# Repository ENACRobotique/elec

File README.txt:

Repository for electronic circuits design

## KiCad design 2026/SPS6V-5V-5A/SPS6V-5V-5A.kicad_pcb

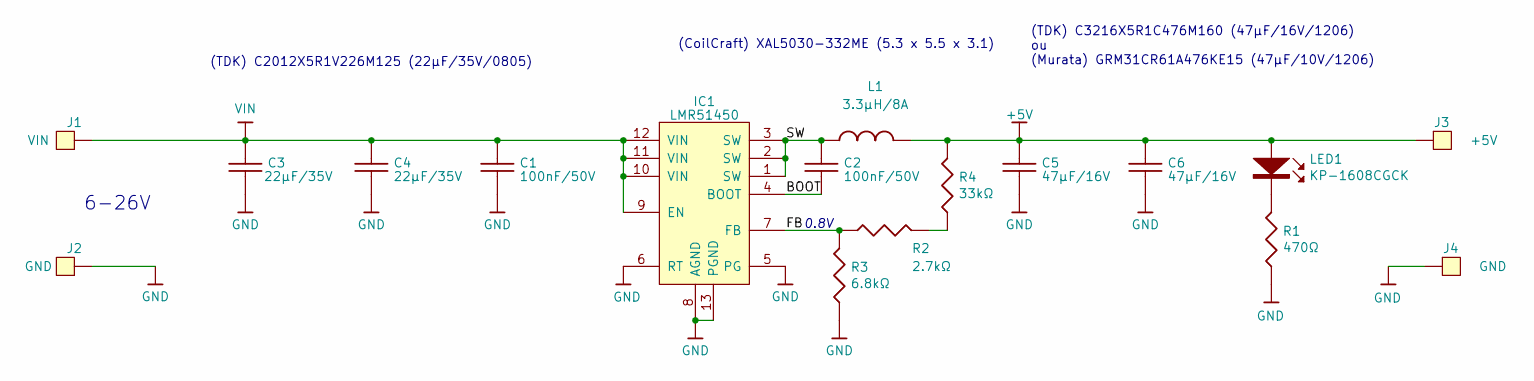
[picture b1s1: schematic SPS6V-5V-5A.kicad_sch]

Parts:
C1, C2: 100nF/50V; C_0603
C3, C4: 22µF/35V; C_0805
C5, C6: 47µF/16V; C_1206
IC1: LMR51450
J1: VIN; power_PAD_THT
J2, J4: GND; power_PAD_THT
J3: +5V; power_PAD_THT
L1: 3.3µH/8A; XAL5030
LED1: KP-1608CGCK
R1: 470Ω; R_0603
R2: 2.7kΩ; R_0603
R3: 6.8kΩ; R_0603
R4: 33kΩ; R_0603

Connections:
+5V: C5.1, C6.1, J3.1, L1.2, LED1.2 (A), R4.1
/BOOT: C2.2, IC1.4 (BOOT)
/FB: IC1.7 (FB), R2.2, R3.1
/SW: C2.1, IC1.1 (SW), IC1.2 (SW), IC1.3 (SW), L1.1
GND: C1.2, C3.2, C4.2, C5.2, C6.2, IC1.5 (PG), IC1.6 (RT), IC1.8 (AGND), IC1.13 (PGND), J2.1, J4.1, R1.2, R3.2
unnamed: LED1.1 (K), R1.1
unnamed: R2.1, R4.2
VIN: C1.1, C3.1, C4.1, IC1.9 (EN), IC1.10 (VIN), IC1.11 (VIN), IC1.12 (VIN), J1.1

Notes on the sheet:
(TDK) C2012X5R1V226M125 (22µF/35V/0805)
(TDK) C3216X5R1C476M160 (47µF/16V/1206) ou (Murata) GRM31CR61A476KE15 (47µF/10V/1206)
(CoilCraft) XAL5030-332ME (5.3 x 5.5 x 3.1)
6-26V
0.8V

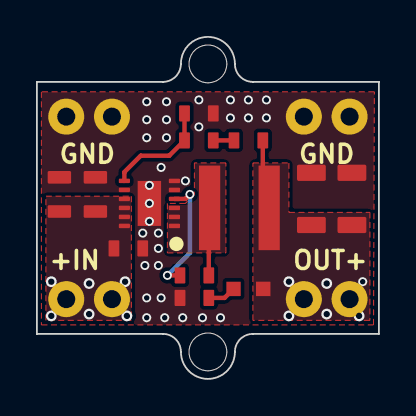
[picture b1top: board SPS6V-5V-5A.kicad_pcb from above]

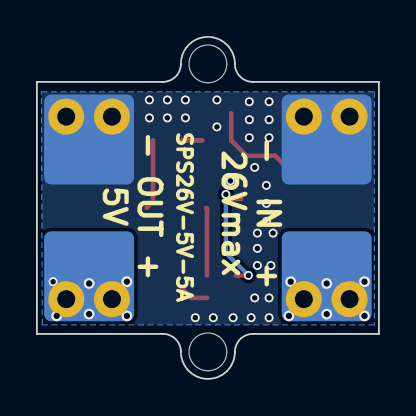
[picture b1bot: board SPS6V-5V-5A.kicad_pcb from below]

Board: 2 copper layers, 19.0 x 19.0 mm, 17 parts (4 on the bottom side), 8 nets.

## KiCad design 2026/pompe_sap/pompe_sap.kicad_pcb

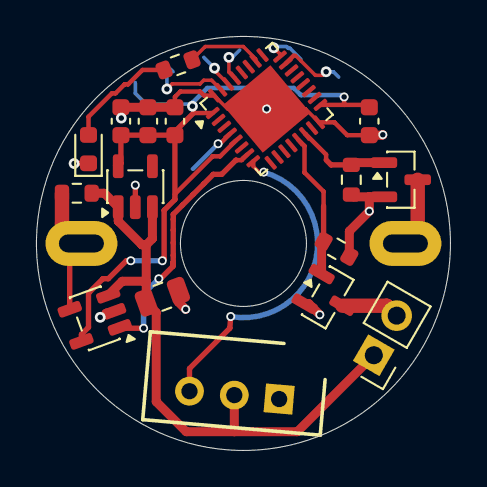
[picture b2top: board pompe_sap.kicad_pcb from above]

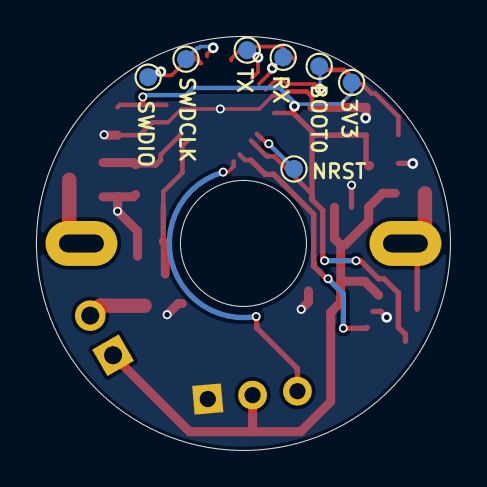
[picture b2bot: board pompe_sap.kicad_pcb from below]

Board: 2 copper layers, 23.0 x 23.0 mm, 25 parts (7 on the bottom side), 18 nets.

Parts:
C1: C 1uf; C_0805_2012Metric
C2: C 1uf; C_0603_1608Metric
C3: 4U7; C_0603_1608Metric
C4, C5: 100n; C_0603_1608Metric
D1: LED; LED_0603_1608Metric
J1: Conn_01x02_Pin; PinHeader_1x02_P2.54mm_Vertical
J2: 22-03-5035; SHDR3W70P0X250_1X3_990X490X590P
Q1, Q2: IRLML6344 (modèle du 6244); SOT-23
R1: Rsens; R_0603_1608Metric
R2: 390; R_0603_1608Metric
R4, R5: 100K; R_0603_1608Metric
TP1: SWDIO_TP; TestPoint_Pad_D1.0mm
TP2: SWDCLK_TP; TestPoint_Pad_D1.0mm
TP3: NRST_TP; TestPoint_Pad_D1.0mm
TP4: 3V3_TP; TestPoint_Pad_D1.0mm
TP5: BOOT0_TP; TestPoint_Pad_D1.0mm
TP6: U1_TX; TestPoint_Pad_D1.0mm
TP7: U1_RX; TestPoint_Pad_D1.0mm
U1: pompe
U2: NCP718xSN120; SOT-23-5
U3: INA180A1; SOT-23-5
U4: STM32L432KCUx; QFN-32-1EP_5x5mm_P0.5mm_EP3.45x3.45mm

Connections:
+3V3: C2.1, C3.1, C4.1, C5.1, TP4.1, U2.5 (OUT), U3.5 (V+), U4.1 (VDD), U4.5 (VDDA), U4.17 (VDD)
+12V: C1.1, J1.1, J2.2, R1.1, U2.1 (IN), U2.3 (EN), U3.3 (+)
/BOOT0: TP5.1, U4.31 (PH3)
/NRST: TP3.1, U4.4 (NRST)
/SWDCLK: TP2.1, U4.24 (PA14)
/SWDIO: TP1.1, U4.23 (PA13)
GND: C1.2, C2.2, C3.2, C4.2, C5.2, D1.1 (K), J2.1, Q1.2 (S), Q2.2 (S), R4.2, R5.2, U2.2 (GND), U3.2 (GND), U4.16 (VSS), U4.32 (VSS), U4.33 (VSS)
unnamed: D1.2 (A), R2.1
unnamed: J1.2, Q2.3 (D)
unnamed: Q1.3 (D), U1.2
unnamed: R1.2, U1.1, U3.4 (-)
unnamed: R2.2, U4.26 (PB3)
unnamed: TP6.1, U4.29 (PB6)
unnamed: TP7.1, U4.30 (PB7)
PUMP: Q1.1 (G), R4.1, U4.14 (PB0)
UART_TX: J2.3, U4.8 (PA2)
VALVE: Q2.1 (G), R5.1, U4.13 (PA7)
Vout: U3.1, U4.7 (PA1)

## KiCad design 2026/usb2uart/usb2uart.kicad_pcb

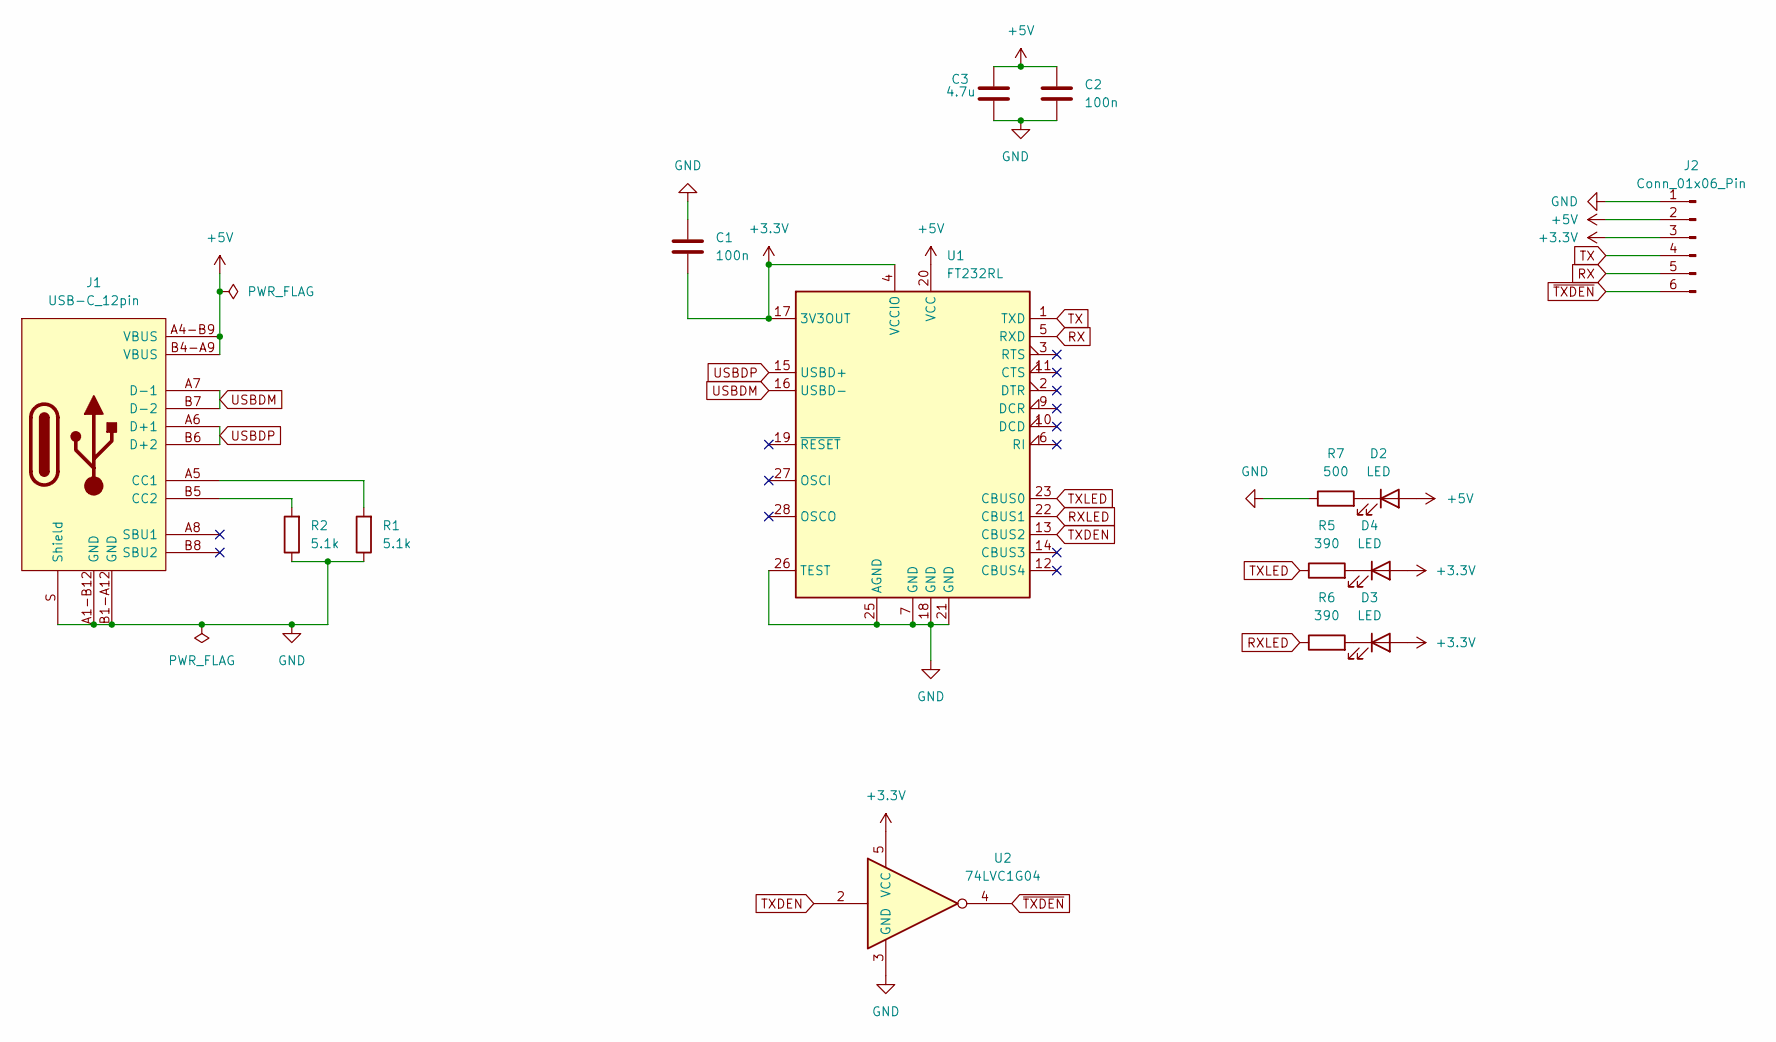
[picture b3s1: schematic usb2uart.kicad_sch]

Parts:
C1, C2: 100n; C_0603_1608Metric
C3: 4.7u; CP_EIA-3216-18_Kemet-A
D2, D3, D4: LED; LED_0603_1608Metric
J1: USB-C_12pin; USB-C_HRO_C-31-M-12
J2: Conn_01x06_Pin; Molex_PicoBlade_53047-0610_1x06_P1.25mm_Vertical
R1, R2: 5.1k; R_0603_1608Metric
R5, R6: 390; R_0603_1608Metric
R7: 500; R_0603_1608Metric
U1: FT232RL; SSOP-28_5.3x10.2mm_P0.65mm
U2: 74LVC1G04; SOT-23-5

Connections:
+3.3V: C1.2, D3.2 (A), D4.2 (A), J2.3, U1.4 (VCCIO), U1.17 (3V3OUT), U2.5 (VCC)
+5V: C2.1, C3.2, D2.2 (A), J1.A4-B9 (VBUS), J1.B4-A9 (VBUS), J2.2, U1.20 (VCC)
GND: C1.1, C2.2, C3.1, J1.A1-B12 (GND), J1.B1-A12 (GND), J1.S (Shield), J2.1, R1.1, R2.1, R7.1, U1.7 (GND), U1.18 (GND), U1.21 (GND), U1.25 (AGND), U1.26 (TEST), U2.3 (GND)
unnamed: D2.1 (K), R7.2
unnamed: D3.1 (K), R6.2
unnamed: D4.1 (K), R5.2
unnamed: J1.A5 (CC1), R1.2
unnamed: J1.B5 (CC2), R2.2
RX: J2.5, U1.5 (RXD)
RXLED: R6.1, U1.22 (CBUS1)
TX: J2.4, U1.1 (TXD)
TXDEN: U1.13 (CBUS2), U2.2
TXLED: R5.1, U1.23 (CBUS0)
USBDM: J1.A7 (D-1), J1.B7 (D-2), U1.16 (USBD-)
USBDP: J1.A6 (D+1), J1.B6 (D+2), U1.15 (USBD+)
~TXDEN: J2.6, U2.4

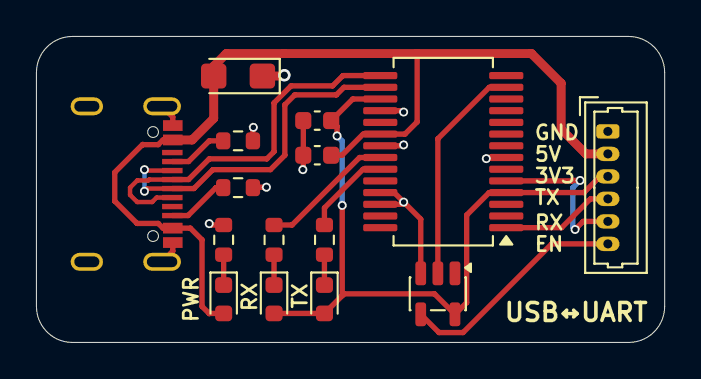
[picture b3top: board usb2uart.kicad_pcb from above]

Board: 2 copper layers, 34.9 x 17.0 mm, 15 parts (0 on the bottom side), 16 nets.

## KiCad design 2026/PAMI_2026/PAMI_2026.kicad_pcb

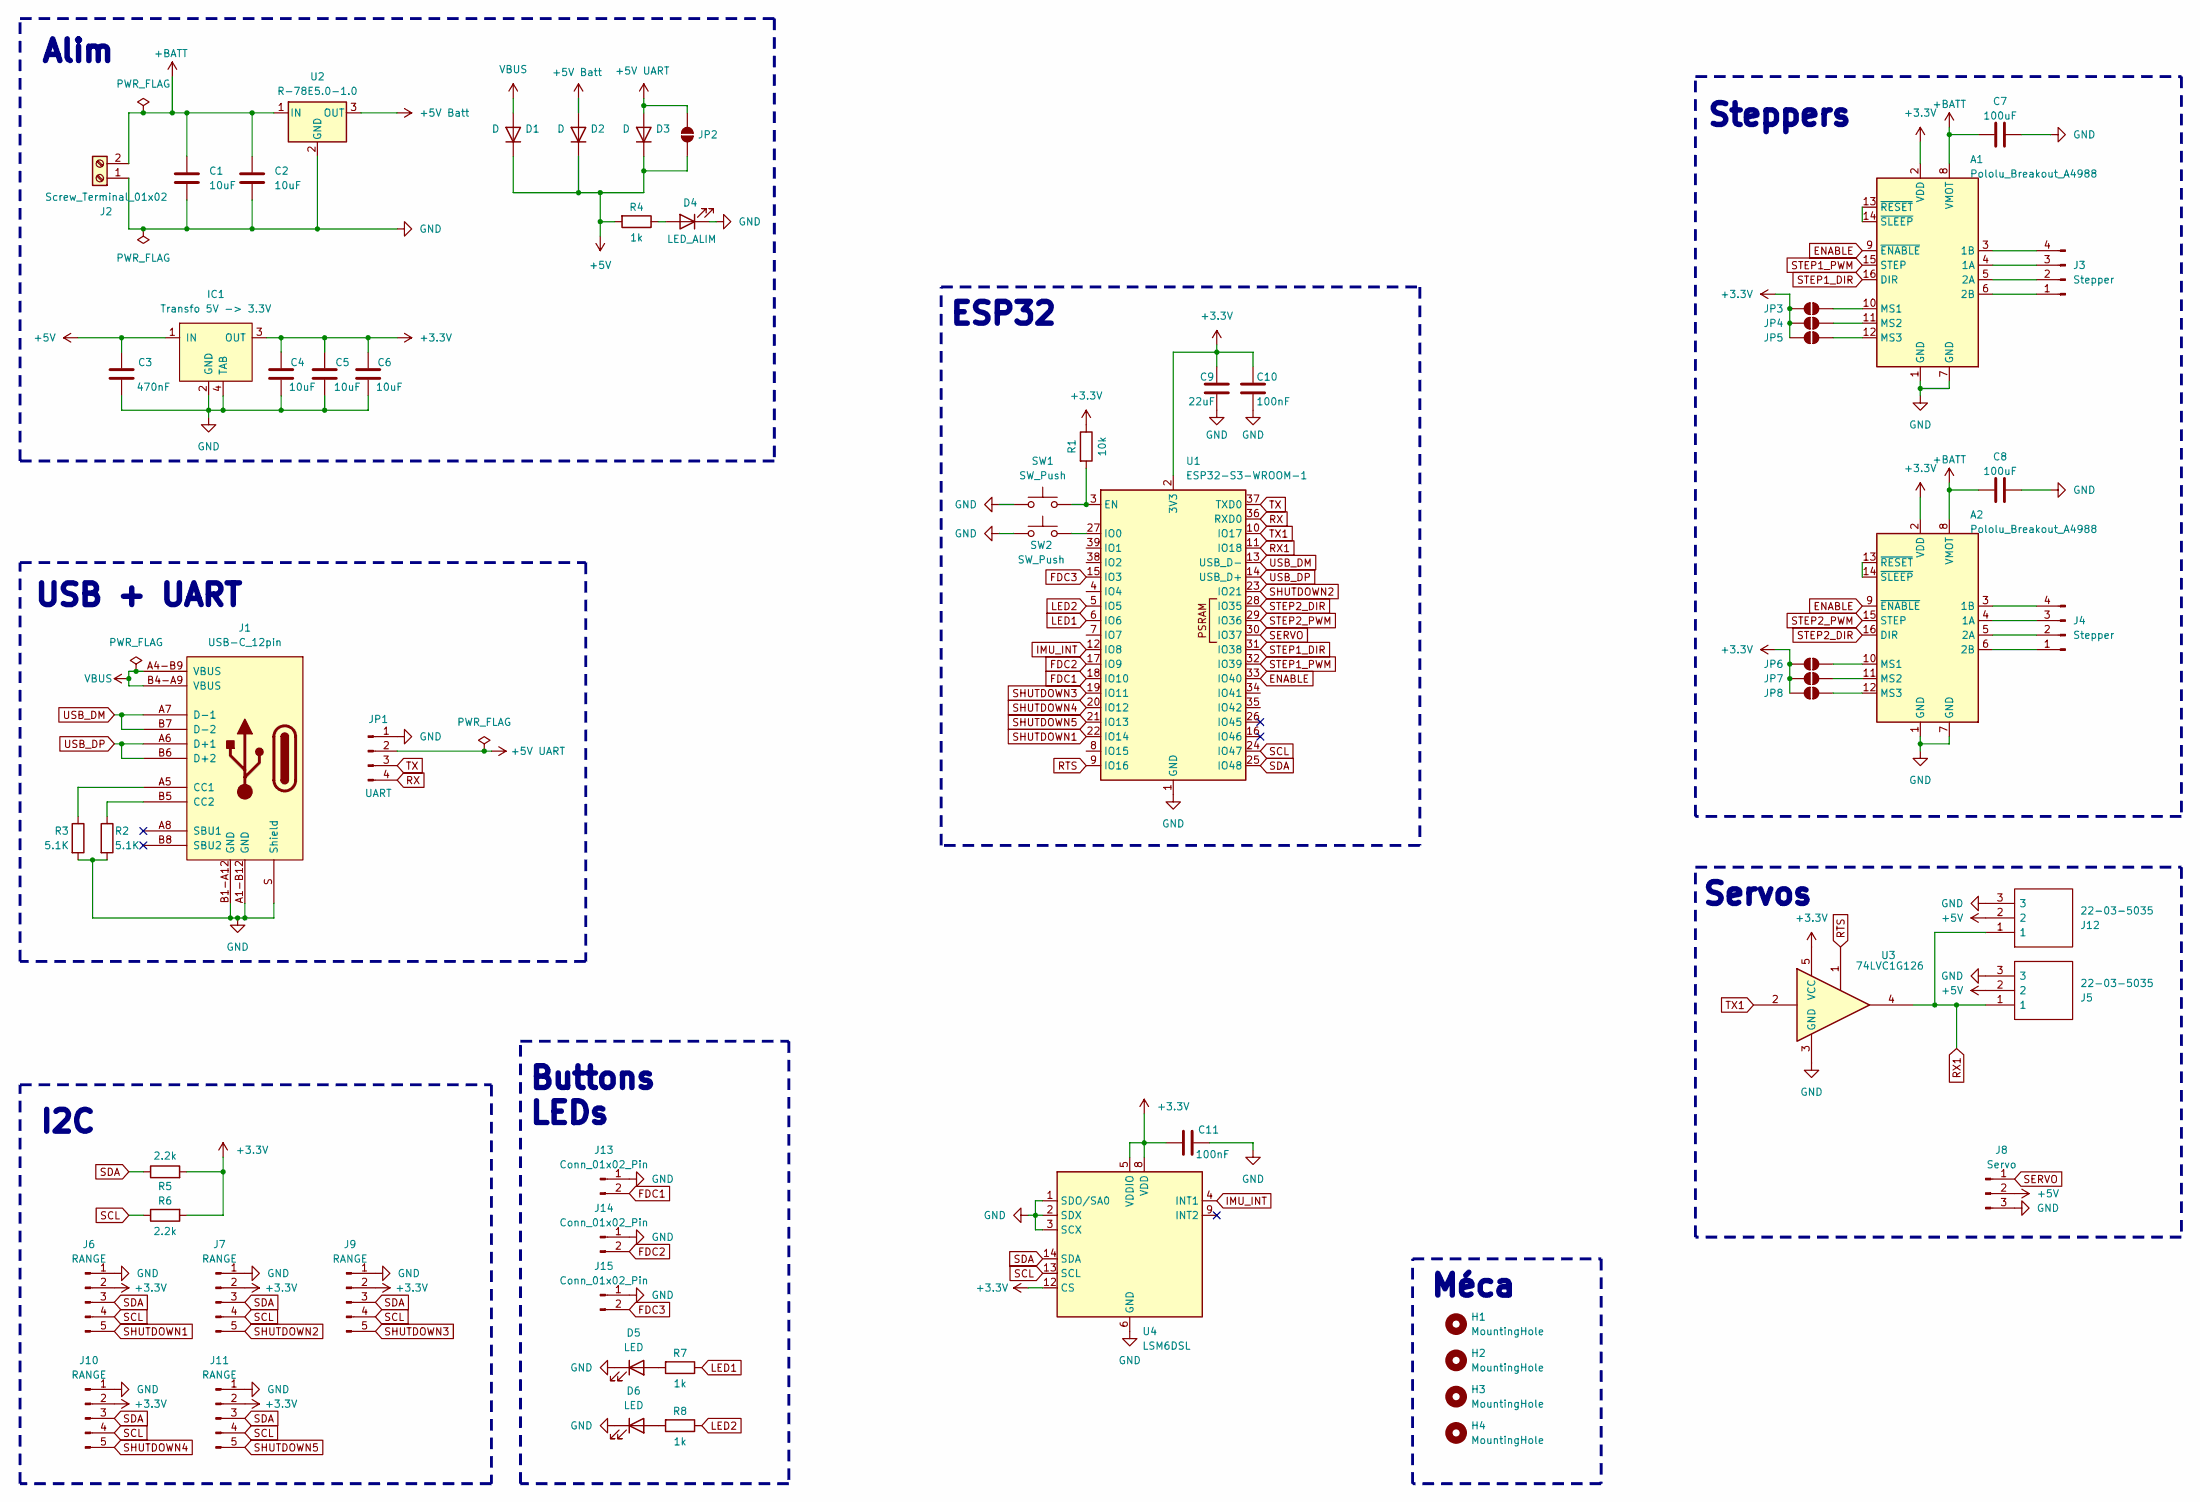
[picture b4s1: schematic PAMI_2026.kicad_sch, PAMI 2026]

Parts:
A1, A2: Pololu_Breakout_A4988; Pololu_Breakout-16_15.2x20.3mm
C1, C2: 10uF; C_0805_2012Metric
C3: 470nF; C_0603_1608Metric
C4, C5, C6: 10uF; C_0603_1608Metric
C7, C8: 100uF; CP_Elec_10x12.5
C9: 22uF; C_0805_2012Metric
C10, C11: 100nF; C_0603_1608Metric
D1, D2, D3: D; Nexperia_CFP3_SOD-123W
D4: LED_ALIM; LED_0603_1608Metric
D5, D6: LED; LED_0603_1608Metric
H1, H2, H3, H4: MountingHole; MountingHole_3.2mm_M3
IC1: Transfo 5V -> 3.3V; LM3940IMP
J1: USB-C_12pin; USB-C_HRO_C-31-M-12
J2: Screw_Terminal_01x02; TerminalBlock_MetzConnect_Type055_RT01502HDWU_1x02_P5.00mm_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
J3, J4: Stepper; PinHeader_1x04_P2.54mm_Vertical
J5, J12: 22-03-5035; SHDR3W70P0X250_1X3_990X490X590P; Manufacturer_Part_Number 22-03-5035; Mouser Part Number 538-22-03-5035
J6, J7, J9, J10, J11: RANGE; Molex_PicoBlade_53398-0571_1x05-1MP_P1.25mm_Vertical
J8: Servo; PinHeader_1x03_P2.54mm_Vertical
J13, J14, J15: Conn_01x02_Pin; PinHeader_1x02_P2.54mm_Vertical
JP1: UART; PinHeader_1x04_P2.54mm_Vertical
JP2: SolderJumper_2_Open; PinHeader_1x02_P2.54mm_Vertical
JP3, JP4, JP5, JP6, JP7, JP8: SolderJumper_2_Open; SolderJumper-2_P1.3mm_Open_TrianglePad1.0x1.5mm
R1: 10k; R_0603_1608Metric
R2, R3: 5.1K; R_0603_1608Metric
R4, R7, R8: 1k; R_0603_1608Metric
R5, R6: 2.2k; R_0603_1608Metric
SW1, SW2: SW_Push; SWITCH_DTSM31NV
U1: ESP32-S3-WROOM-1
U2: R-78E5.0-1.0; Converter_DCDC_RECOM_R-78E-0.5_THT
U3: 74LVC1G126; SOT-23-5
U4: LSM6DSL; LGA-14_3x2.5mm_P0.5mm_LayoutBorder3x4y

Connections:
+3.3V: A1.2 (VDD), A2.2 (VDD), C4.1, C5.1, C6.1, C9.1, C10.1, C11.1, IC1.3 (OUT), J6.2, J7.2, J9.2, J10.2, J11.2, JP3.1 (A), JP4.1 (A), JP5.1 (A), JP6.1 (A), JP7.1 (A), JP8.1 (A), R1.1, R5.2, R6.2, U1.2 (3V3), U3.5 (VCC), U4.5 (VDDIO), U4.8 (VDD), U4.12 (CS)
+5V: C3.1, D1.1 (K), D2.1 (K), D3.1 (K), IC1.1 (IN), J5.2, J8.2, J12.2, JP2.1 (A), R4.2
+5V Batt: D2.2 (A), U2.3 (OUT)
+5V UART: D3.2 (A), JP1.2, JP2.2 (B)
+BATT: A1.8 (VMOT), A2.8 (VMOT), C1.1, C2.1, C7.1, C8.1, J2.2, U2.1 (IN)
ENABLE: A1.9 (~ENABLE), A2.9 (~ENABLE), U1.33 (IO40)
FDC1: J13.2, U1.18 (IO10)
FDC2: J14.2, U1.17 (IO9)
FDC3: J15.2, U1.15 (IO3)
GND: A1.1 (GND), A1.7 (GND), A2.1 (GND), A2.7 (GND), C1.2, C2.2, C3.2, C4.2, C5.2, C6.2, C7.2, C8.2, C9.2, C10.2, C11.2, D4.1 (K), D5.1 (K), D6.1 (K), IC1.2 (GND), IC1.4 (TAB), J1.A1-B12 (GND), J1.B1-A12 (GND), J1.S (Shield), J2.1, J5.3, J6.1, J7.1, J8.3, J9.1, J10.1, J11.1, J12.3, J13.1, J14.1, J15.1, JP1.1, R2.2, R3.2, SW1.1, SW2.1, U1.1 (GND), U1.40 (GND), U1.41 (GND), U2.2 (GND), U3.3 (GND), U4.1 (SDO/SA0), U4.2 (SDX), U4.3 (SCX), U4.6 (GND), U4.7 (GND)
IMU_INT: U1.12 (IO8), U4.4 (INT1)
LED1: R7.1, U1.6 (IO6)
LED2: R8.1, U1.5 (IO5)
unnamed: A1.4 (1A), J3.3
unnamed: A1.3 (1B), J3.4
unnamed: A1.5 (2A), J3.2
unnamed: A1.6 (2B), J3.1
unnamed: A1.10 (MS1), JP3.2 (B)
unnamed: A1.11 (MS2), JP4.2 (B)
unnamed: A1.12 (MS3), JP5.2 (B)
unnamed: A1.13 (~RESET), A1.14 (~SLEEP)
unnamed: A2.4 (1A), J4.3
unnamed: A2.3 (1B), J4.4
unnamed: A2.5 (2A), J4.2
unnamed: A2.6 (2B), J4.1
unnamed: A2.10 (MS1), JP6.2 (B)
unnamed: A2.11 (MS2), JP7.2 (B)
unnamed: A2.12 (MS3), JP8.2 (B)
unnamed: A2.13 (~RESET), A2.14 (~SLEEP)
unnamed: D4.2 (A), R4.1
unnamed: D5.2 (A), R7.2
unnamed: D6.2 (A), R8.2
unnamed: J1.A5 (CC1), R3.1
unnamed: J1.B5 (CC2), R2.1
unnamed: R1.2, SW1.2, U1.3 (EN)
unnamed: SW2.2, U1.27 (IO0)
RTS: U1.9 (IO16), U3.1
RX: JP1.4, U1.36 (RXD0)
RX1: J5.1, J12.1, U1.11 (IO18), U3.4
SCL: J6.4, J7.4, J9.4, J10.4, J11.4, R6.1, U1.24 (IO47), U4.13 (SCL)
SDA: J6.3, J7.3, J9.3, J10.3, J11.3, R5.1, U1.25 (IO48), U4.14 (SDA)
SERVO: J8.1, U1.30 (IO37)
SHUTDOWN1: J6.5, U1.22 (IO14)
SHUTDOWN2: J7.5, U1.23 (IO21)
SHUTDOWN3: J9.5, U1.19 (IO11)
SHUTDOWN4: J10.5, U1.20 (IO12)
SHUTDOWN5: J11.5, U1.21 (IO13)
STEP1_DIR: A1.16 (DIR), U1.31 (IO38)
STEP1_PWM: A1.15 (STEP), U1.32 (IO39)
STEP2_DIR: A2.16 (DIR), U1.28 (IO35)
STEP2_PWM: A2.15 (STEP), U1.29 (IO36)
TX: JP1.3, U1.37 (TXD0)
TX1: U1.10 (IO17), U3.2
USB_DM: J1.A7 (D-1), J1.B7 (D-2), U1.13 (USB_D-)
USB_DP: J1.A6 (D+1), J1.B6 (D+2), U1.14 (USB_D+)
VBUS: D1.2 (A), J1.A4-B9 (VBUS), J1.B4-A9 (VBUS)

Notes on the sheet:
USB + UART
I2C
Buttons LEDs
Steppers
ESP32
Méca
Alim
Servos

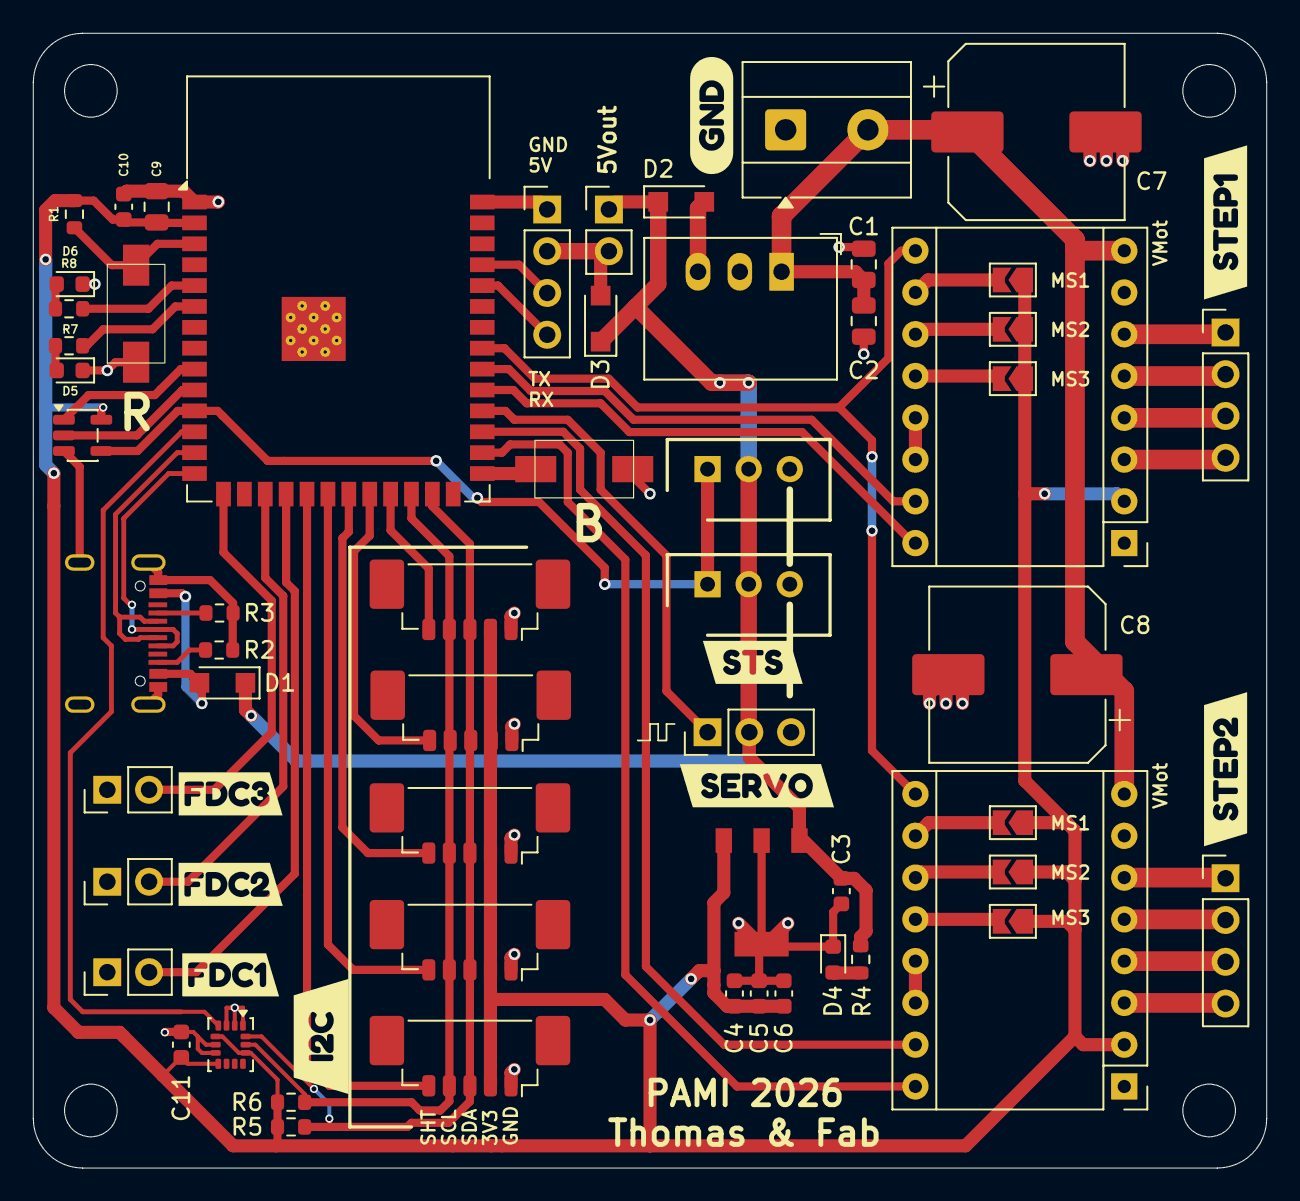
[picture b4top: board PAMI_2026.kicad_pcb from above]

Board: 2 copper layers, 75.0 x 69.0 mm, 70 parts (0 on the bottom side), 56 nets.

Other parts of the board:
kibuzzard-693B43A5: G***; kibuzzard-693B43A5
kibuzzard-693B44DB: G***; kibuzzard-693B44DB
kibuzzard-693B44EC: G***; kibuzzard-693B44EC
kibuzzard-693B45E1: G***; kibuzzard-693B45E1
kibuzzard-693B45FB: G***; kibuzzard-693B45FB
kibuzzard-693B4393: G***; kibuzzard-693B4393
kibuzzard-693B4464: G***; kibuzzard-693B4464
kibuzzard-693B4516: G***; kibuzzard-693B4516
kibuzzard-693B4601: G***; kibuzzard-693B4601

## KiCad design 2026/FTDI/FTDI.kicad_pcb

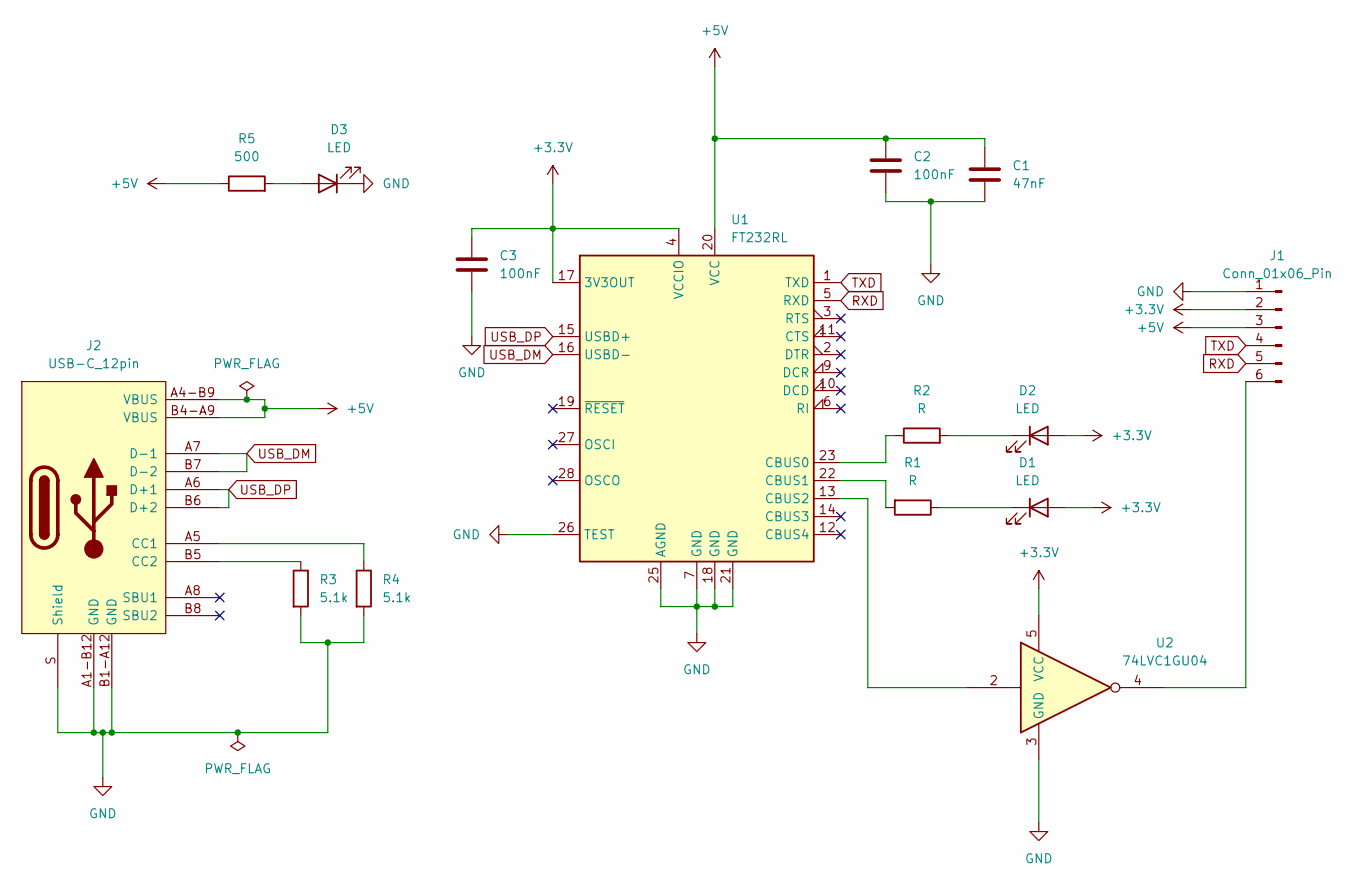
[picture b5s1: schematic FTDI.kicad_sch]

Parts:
C1: 47nF; C_0603_1608Metric
C2, C3: 100nF; C_0603_1608Metric
D1, D2, D3: LED; LED_0603_1608Metric
J1: Conn_01x06_Pin; Molex_PicoBlade_53047-0610_1x06_P1.25mm_Vertical
J2: USB-C_12pin; USB-C_HRO_C-31-M-12
R1, R2: R; R_0603_1608Metric
R3, R4: 5.1k; R_0603_1608Metric
R5: 500; R_0603_1608Metric
U1: FT232RL; SSOP-28_5.3x10.2mm_P0.65mm
U2: 74LVC1GU04; SOT-353_SC-70-5

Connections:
+3.3V: C3.1, D1.2 (A), D2.2 (A), J1.2, U1.4 (VCCIO), U1.17 (3V3OUT), U2.5 (VCC)
+5V: C1.1, C2.1, J1.3, J2.A4-B9 (VBUS), J2.B4-A9 (VBUS), R5.1, U1.20 (VCC)
GND: C1.2, C2.2, C3.2, D3.1 (K), J1.1, J2.A1-B12 (GND), J2.B1-A12 (GND), J2.S (Shield), R3.2, R4.2, U1.7 (GND), U1.18 (GND), U1.21 (GND), U1.25 (AGND), U1.26 (TEST), U2.3 (GND)
unnamed: D1.1 (K), R1.1
unnamed: D2.1 (K), R2.2
unnamed: D3.2 (A), R5.2
unnamed: J1.6, U2.4
unnamed: J2.A5 (CC1), R4.1
unnamed: J2.B5 (CC2), R3.1
unnamed: R2.1, U1.23 (CBUS0)
unnamed: R1.2, U1.22 (CBUS1)
unnamed: U1.13 (CBUS2), U2.2
RXD: J1.5, U1.5 (RXD)
TXD: J1.4, U1.1 (TXD)
USB_DM: J2.A7 (D-1), J2.B7 (D-2), U1.16 (USBD-)
USB_DP: J2.A6 (D+1), J2.B6 (D+2), U1.15 (USBD+)

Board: 2 copper layers, 15 parts (0 on the bottom side), 16 nets, no tracks yet.

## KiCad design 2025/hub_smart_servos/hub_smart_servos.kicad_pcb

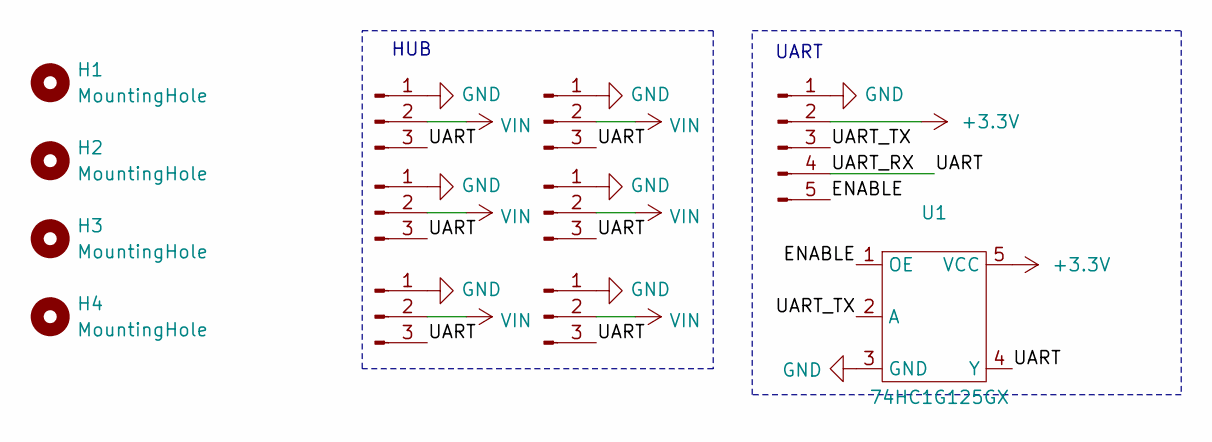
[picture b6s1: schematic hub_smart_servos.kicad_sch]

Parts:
H1, H2, H3, H4: MountingHole; MountingHole_3.2mm_M3
J1, J2, J3, J4, J5, J6: Conn_01x03_Pin; Molex_SPOX_5267-03A_1x03_P2.50mm_Vertical
J8: Conn_01x05_Pin; Molex_PicoBlade_53047-0510_1x05_P1.25mm_Vertical
U1: SOT-353_SC-70-5

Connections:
+3.3V: J8.2, U1.5 (VCC)
/ENABLE: J8.5, U1.1 (OE)
/UART: J1.3, J2.3, J3.3, J4.3, J5.3, J6.3, J8.4, U1.4 (Y)
/UART_TX: J8.3, U1.2 (A)
GND: J1.1, J2.1, J3.1, J4.1, J5.1, J6.1, J8.1, U1.3 (GND)
VIN: J1.2, J2.2, J3.2, J4.2, J5.2, J6.2

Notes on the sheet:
UART
HUB

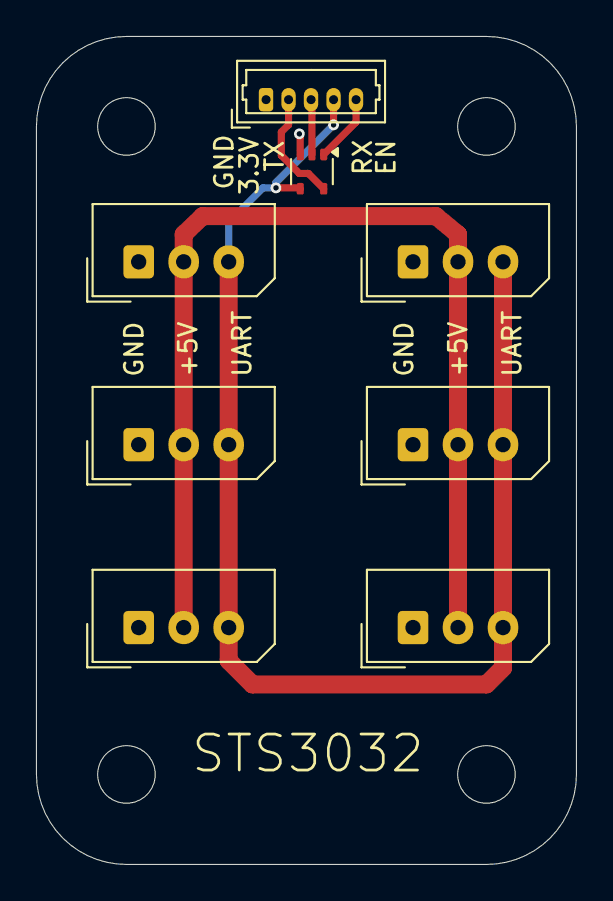
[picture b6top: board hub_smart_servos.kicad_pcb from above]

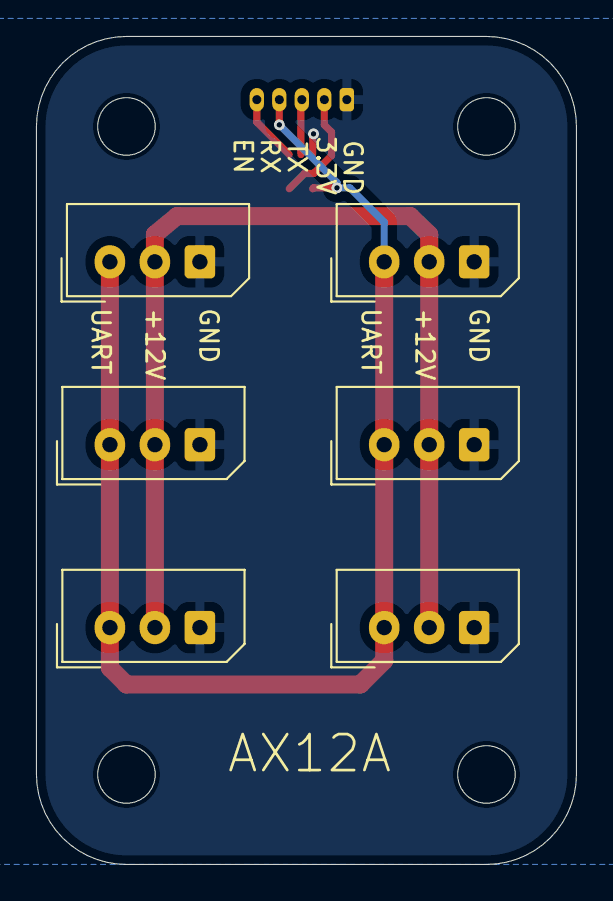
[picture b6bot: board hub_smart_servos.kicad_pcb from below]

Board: 2 copper layers, 30.0 x 46.0 mm, 18 parts (6 on the bottom side), 6 nets.

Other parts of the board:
J11, J12, J13, J14, J15, J16: Conn_01x03_Pin; Molex_SPOX_5267-03A_1x03_P2.50mm_Vertical

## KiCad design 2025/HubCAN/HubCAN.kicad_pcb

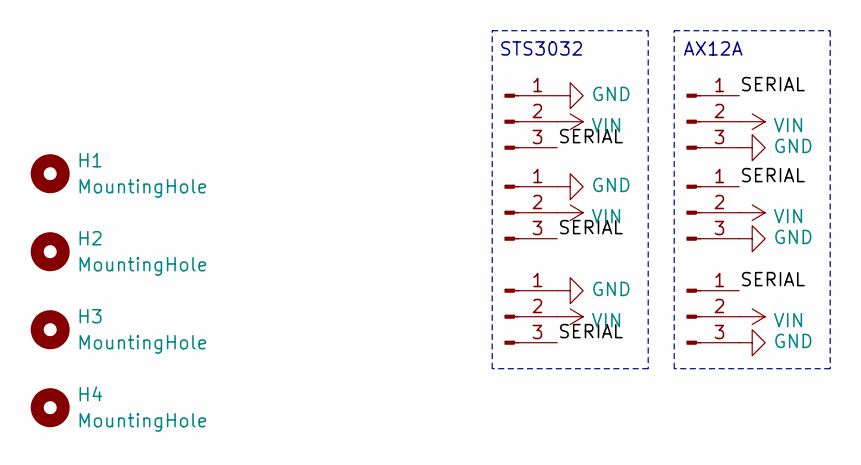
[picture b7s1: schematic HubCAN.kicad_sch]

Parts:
H1, H2, H3, H4: MountingHole; MountingHole_3.2mm_M3
J1, J2, J3, J4, J5, J6: Conn_01x03_Pin; Molex_SPOX_5267-03A_1x03_P2.50mm_Vertical

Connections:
/SERIAL: J1.3, J2.3, J3.3, J4.1, J5.1, J6.1
GND: J1.1, J2.1, J3.1, J4.3, J5.3, J6.3
VIN: J1.2, J2.2, J3.2, J4.2, J5.2, J6.2

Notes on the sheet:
AX12A
STS3032

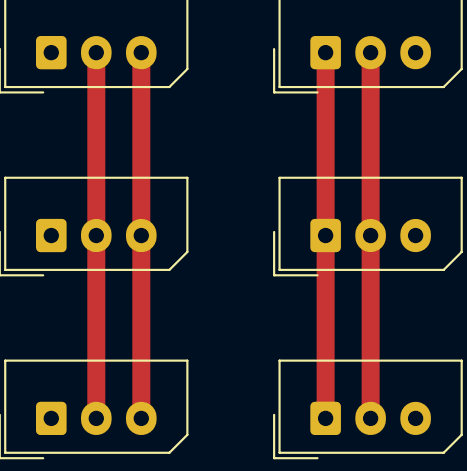
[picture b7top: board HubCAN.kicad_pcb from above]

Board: 2 copper layers, 10 parts (0 on the bottom side), 3 nets.

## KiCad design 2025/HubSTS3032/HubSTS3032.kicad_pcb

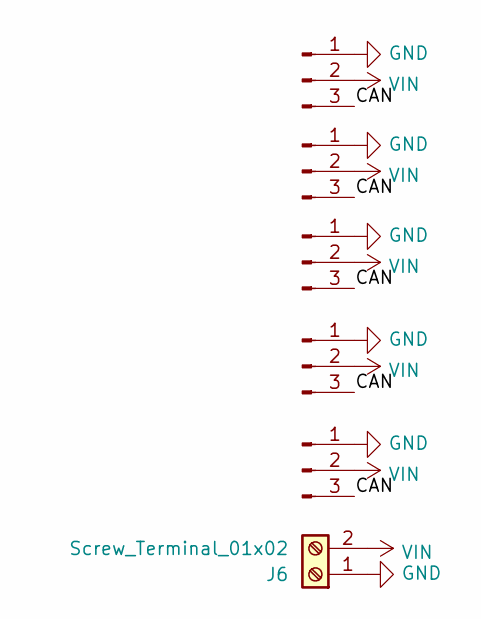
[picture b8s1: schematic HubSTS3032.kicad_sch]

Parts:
J1, J2, J3, J4, J5: Conn_01x03_Pin; Molex_SPOX_5267-03A_1x03_P2.50mm_Vertical
J6: Screw_Terminal_01x02; TerminalBlock_bornier-2_P5.08mm

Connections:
/CAN: J1.3, J2.3, J3.3, J4.3, J5.3
GND: J1.1, J2.1, J3.1, J4.1, J5.1, J6.1
VIN: J1.2, J2.2, J3.2, J4.2, J5.2, J6.2

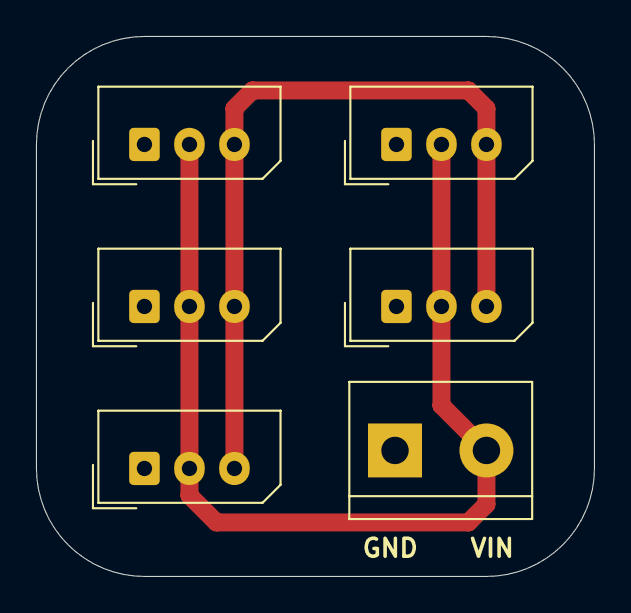
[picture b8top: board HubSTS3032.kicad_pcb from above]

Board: 2 copper layers, 31.0 x 30.0 mm, 6 parts (0 on the bottom side), 3 nets.

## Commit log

2015-03-24 [primary_robot] Adds AI/IO board
2015-03-24 [primary_robot] Adds control + power boards Rev1
2015-03-24 [prop_tripod] Updates to pre-Rev2
2015-03-24 [prop-tripod] Update the footprint of the LPC, increase the readability of some name on the board
2015-03-25 [secondary_robot] Adds shematics and board
2015-03-25 [tester] adds shematics and board
2015-03-25 [secondary & tester] remove useless files and move bad located files
2015-03-27 [prop_tripod] Fixes RST connection
2015-04-01 [prop_tripod] Fixes buffer pull-ups + I²C pull-ups headers
2015-04-01 [prop_tripod] Removes useless buffer
2015-04-02 [prop_tripod] Changes pin asssignation
2015-04-03 [tester] add VCC pin for UART
2015-04-03 [tester] create ihm board
2015-04-04 [Programmer ICSP Atmega328p]
2015-04-04 [Programmer ICSP Atmega328p] smaller design
2015-04-04 Add gitignore to ignore .b#, .s#, pdf & epf files. Usefull for everyone.
2015-04-08 [Programmer ICSP Atmega328p] optimise routing
2015-04-08 [tester]move holes to make a good design
2015-04-14 [primary_robot] Adds C2014 R1 Arduino IO shield
2015-04-14 [priom/io] Updates some labels
2015-04-23 [primary_robot] Fixes Uart2 to Uart1 on the BBB
2015-05-05 [2014] Adds 2014 main elec
2015-05-17 [tester] modify to V2 Alpha.
2015-05-17 [tester] improve V2.
2015-05-17 [tester] add pins correspondance.
2015-05-18 [tester] add "pont diviseur" and some modification.
2015-05-21 [Arduino_like] add arduino like board.
2015-05-21 [Arduino_like] modify board.
2015-05-21 [Arduino_like] adds GND, VCC and AREF pins.
2015-05-31 [Arduino like] move on 0.1 inch grid.
2015-06-01 [Arduino like] align pins.
2015-06-01 [Arduino_like] align power.
2015-06-01 [arduino like] move via.
2015-06-01 [Arduino_like] add reset pin.
2015-06-01 [Arduino_like] move text.
2015-06-02 [Tester] new design.
2015-06-02 [tester] continue new design.
2015-06-02 [Arduino_like] change some dimensions.
2015-06-02 [tester] improve design.
2015-06-03 [Arduino_like] V0.1a
2015-06-03 [tester] V2.0a
2015-06-17 [Arduino_like] move labels to the right place.
2015-10-29 [Multitask attiny85] initial commit.
2015-10-29 [tester] modify pin configuration.
2015-10-30 [tester] Begin new design.
2015-10-30 [tester] finish design V3.
2015-10-30 [tester] improve 3rd design.
2015-10-30 [tester] add some measures.
2015-11-02 [tester] puts some wire in top.
2015-11-02 [tester] optimize some routes.
2015-11-02 [tester] keep separation between components.
2015-11-02 [tester] separate some vias.
2015-11-02 [tester] separate other routes.
2015-11-02 [Programmer ICSP Atmega328p] add capa values.
2015-11-03 [elec aiio] Adds a library with raspberry component
2015-11-03 [elec AIIO] Updates the old AIIO card to match the 2016 requirements, rasperry socket, IHM on ard, bluetooth socket on ard and 5 switch plugs on ard.
2016-02-11 [AIIO] Adds a reset button for the Raspi
2016-02-13 [AIIO_board] Add I2C bus "I2C0" for sonar sensors on shematic file.
2016-02-14 [AIIO board] Remove old .brd and .sch files.
2016-02-14 [AIIO boards] Put files in directories wrt the year.
2016-02-14 [AIIO_boards] Create and add components for IHM_BOARD.
2016-02-15 [AIIO_boards] Clean schematic and board files.
2016-02-15 [AIIO_boards] Update footprint of stage 4.
2016-02-15 [AIIO_board]Place connectors for sonar connectors.
2016-02-15 [AIIO_board]Place RP2 and make corrections on I2C_RP2 bus.
2016-02-16 [AIIO_boards] Connect servo connectors to PCA9685PW.
2016-02-16 [AIIO_board] Make route for sonar I2C
2016-02-16 [AIIO_board] Update pin Ardu
2016-02-16 [AIIO_boards] Route presence connectors.
2016-02-17 [AIIO_boars] Update footprint primary.
2016-02-17 [AIIO_board] Add I2C and UART connectors to Arduino and RP2 boards.
2016-02-17 [AIIO_boards] Add connectors for 5v_SIG and root them.
2016-02-17 [AIIO_board] Route IHM components.
2016-02-18 [AIIO_board] Add 3v3 reglator and connectors on .sch and .board files.
2016-02-21 [AIIO_board] Add button and connector for IHM. Remove useless pull-up resistors.
2016-02-22 [AIIO_board] Update personnal library for primary.
2016-02-22 [AIIO_board] Make correction on .brd file to avoid collsions btw parts.
2016-03-16 [AIIO boards] Make corrections, add components (board) for PCA9685.
2016-03-16 [Arm board] Add board for robotic arm.
2016-03-16 Add example file for CAM Processing (Gerber format).
2016-04-13 [AIIO 2016] Corrects a mistake (5V passing through Arduino A0)
2016-04-24 [Porgrammer ICSP] Make another design for handle Attiny85
2016-04-24 [Programmer ICSP] Add awesome eagle!
2016-09-07 [Programmer ICSP] Really add the eagle.
2016-09-07 [Color sensor] Add first version of color sensor.
2017-04-24 [primary] First 2017 commit.
2017-04-24 cleaning
2017-04-24 [Primary] Erase some componants.
2017-04-24 [primary] connectors board RPi.
2017-04-25 [primary] 2nd version, without mass plane.
2017-04-25 [primary] Adds mass plane.
2017-05-04 [RSPI] Adds schematic
2017-09-29 [Smarties_sorter] Adds schematic and board
2017-09-29 [Smarties_sorter] Adds flyback diode
2017-09-29 [Smarties Sorter] Adds a buck
2017-09-29 [Smarties sorter] Adds screw clamp for battery
2017-09-29 [Smarties Sorter] Adds ground plane.
2017-09-30 [Smarties Sorter] Connects AVCC to 5V + capacitor
2017-10-02 [Smarties_sorter] Change color sensor plug
2017-10-02 [Smarties_sorter] Adds resistor to pull down motor command
2017-10-02 [smarties_sorter] Adds UART plug
2017-10-02 [smarties_sorter] Adds capa on the motor
2017-10-02 [smarties_sorter] Change buck to ls7805 and route everything.
2017-10-06 [libraries] Move libraries to better named directory.
2017-10-06 [Multitask attiny85] Reduce wire width.
2017-10-27 [FAT board] Add schematic file.
2017-10-27 [FAT board] Add readme file.
2017-10-27 [FAT board] Modify specs a bit.
2017-10-27 [FAT board] Adds connector for free pins.
2017-10-27 [libraries] Adds 'diy-modules' library.
2017-10-27 [FAT board] Adds reset button.
2017-10-27 [FAT board] Adds necessary components for H-bridges.
2017-10-27 [FAT board] Change some names.
2017-10-27 [FAT board] Adds UART and I2C connectors.
2017-10-27 [FAT board] Connect motors to teensy and add dynamixel control.
2017-10-27 [FAT board] Adds power supply.
2017-10-27 [FAT board] Begin board.
2017-10-27 [primary] Adds label.
2017-10-27 [TRR] Adds board file.
2017-10-27 [TRR] Adds schematic for the car, TRR 2017.
2017-11-01 Add elec boards for primary robot.
2017-11-01 Complete previous commit.
2017-11-02 [FAT board] Connect additionnal power connectors behind interruptors.
2017-11-03 [FAT board] Route board.
2017-11-04 [FAT board] Correct shematic according to Melvin's comments.
2017-11-04 [FAT board] Modify board to match shematic correction.
2017-11-04 [FAT board] Adds some labels.
2017-11-04 Changed I2C Pull-Up resistor selector to match I2C specifications
    Note: I2C Resistors doesn't have any value yet. Assessment of line
    capacitance is in progress...
2017-11-05 Updated I2C ports and pull-up system to match I2C standard specifications
    Note : Assessment of Pull-Up resistors values is still pending.
2017-11-05 Simplified i2c pull-up selector and Partial routing (77%)
2017-11-06 Finished wiring using top layer jumpers
2017-11-07 Adding board Design Rules
2017-11-08 robot_base.sch/brd: routing complete, clearance increased and checked. Add teensy package with bigger pads.
2017-11-08 Change shape of the pads in a new package version of teensy
2017-11-08 Change shape of the pads for D24V50F5 (buck 5V)
2017-11-08 Update robot_system.sch/brd: Minor corrections in sch and start to route.
2017-11-09 Update and complete routing of robot_system board. Last checks TODO.
2017-11-16 Correction of traces Overlap issues
2017-11-23 [robot_base] Update robot_base and robot_systems boards.
2017-11-23 [robot_base] Update dimensions of robot_base board
2017-12-07 [robot_system] Increase clearance, update package of one condo
2017-12-07 [robot_base] Increase clearance
2017-12-10 [robot_base] Update clearance to 15 mil for wire, pad and via.
2017-12-10 [robot_base] Increase clearance. Better routing.
2017-12-11 Updated DRC file to current rules
2018-01-11 Adding Jevois Module transmission board + schematic
    To be set up on the remote modules
2018-01-11 Adding jevois command module and finishing boards
2018-01-11 Correcting a mismatch between input pins
2018-02-20 Adds librairies.
2018-02-20 [FAT pannal] Adds shematic and board.
2018-02-20 [FAT pannal] Split cavalier in two.
2018-02-21 [FAT pannal] Begins routing.
2018-02-21 [FAT pannal] Continue routing.
2018-02-22 [FAT pannal] Finish board V1.
2018-02-22 [FAT pannal] Adds pdfs.
2018-03-06 [dynamixel board] Adds dynamixel board V1.
2018-03-06 [FAT V2]Begin schematic
2018-03-12 [FAT] begins V2
2018-03-12 [Secondary] Adds the board.
2018-03-12 [secondary] Adds the final board
2018-03-12 [Secondary] Begining of the secondary elec card 2018
2018-03-12 [secondary 2018] Modificates the position of the elements above the x abscisse
2018-03-12 [Secondary] Finishes the 2018 schematic
2018-03-12 [secondary] Adds the final schematic and board
2018-03-12 [Libraries] Adds pth08080
2018-03-13 [FAT V2] Route easy side.
2018-03-13 [FAT V2] Finish board.
2018-10-05 Debut test motor control
2019-04-07 [principal2019] Footprint libs.
2019-04-07 [principal2019] Symbol libs.
2019-04-07 [principal2019] 3d packages.
2019-04-07 [principal2019] Adds project.
2019-04-08 [principal2019] Assigns footprints.
2019-04-10 [principal2019] End of elec.
2019-04-10 [principal2019] Adds lib.
2019-04-10 [principal2019] file .pro
2019-04-10 Adds credentials and PDF.
2020-02-12 Begins elec 2020 robot A.
2020-02-14 Updates elec RobotA2020.
2020-02-19 Adds phare2020 elec.
2020-02-27 finish schematic PCA9685 and robotA
2020-03-06 routing carte_PCA9685
2020-03-08 Correction cartes 2020 robotA
2020-03-12 Fin carte elec 2020 robot-a
2020-09-20 init folder and main card
    add folder for main card and kicad libs
2022-11-26 début carte alim v2
2022-11-26 CarteAlimV2-Suite et fin
2022-11-26 Ajout des libraries de logo
2023-02-02 Ajout des cartes de 2022 + début carte principale 2023
2023-02-02 Ajout de labels sur le schématique, tome1
2023-02-03 Ajout des drivers de steppers + connecté tous les tags
2023-02-08 Schéma carte principale fini
2023-02-08 Ajout de résistances de pullup
2023-02-11 Ajout de la carte du panier
2023-02-16 Suppression d'une carte foireuse
2023-02-16 Carte d'alim V2.5
2023-02-16 Arrondi d'une dernière piste
2023-02-16 arrondis ++
2023-02-16 MAJ cartes elec
2023-02-16 Update finale
2023-02-16 Fin de l'elec
2023-02-27 WARNING ENCODER 1
2025-01-30 [pami 2025] Fin PCB V1
2025-03-14 hub CAN
2025-03-17 Hub CAN WIp
2025-10-17 hub smart servos
2025-10-17 useless box 2025
2025-10-17 schemas FTDI
2025-12-11 [PAMI 2026] Schematics + board.
2025-12-12 [PAMI 2026] Add IMU.
2025-12-13 Pompe SAP
2025-12-18 [usb2uart] Fin de la carte
2025-12-18 [SPS6V-5V-5A] Ajout carte Alim 5V
2026-01-02 [pompe SAP] Ajoute UART debug test points and LED.
2026-01-02 [pompe SAP] panel stencil
2026-01-02 [alim 5V] remplace vias par footprint.
